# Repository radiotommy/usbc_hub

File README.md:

# usbc_hub
A 3-port usb hub.

It's part of my machenical keyboard with integrated hub project. This board stack at the back of my keyboard pcb with a 4 pin header as a usb port connect 
to my keyboard controller.

It's functional except USB3 only works in one orientation on the TypeC connector.

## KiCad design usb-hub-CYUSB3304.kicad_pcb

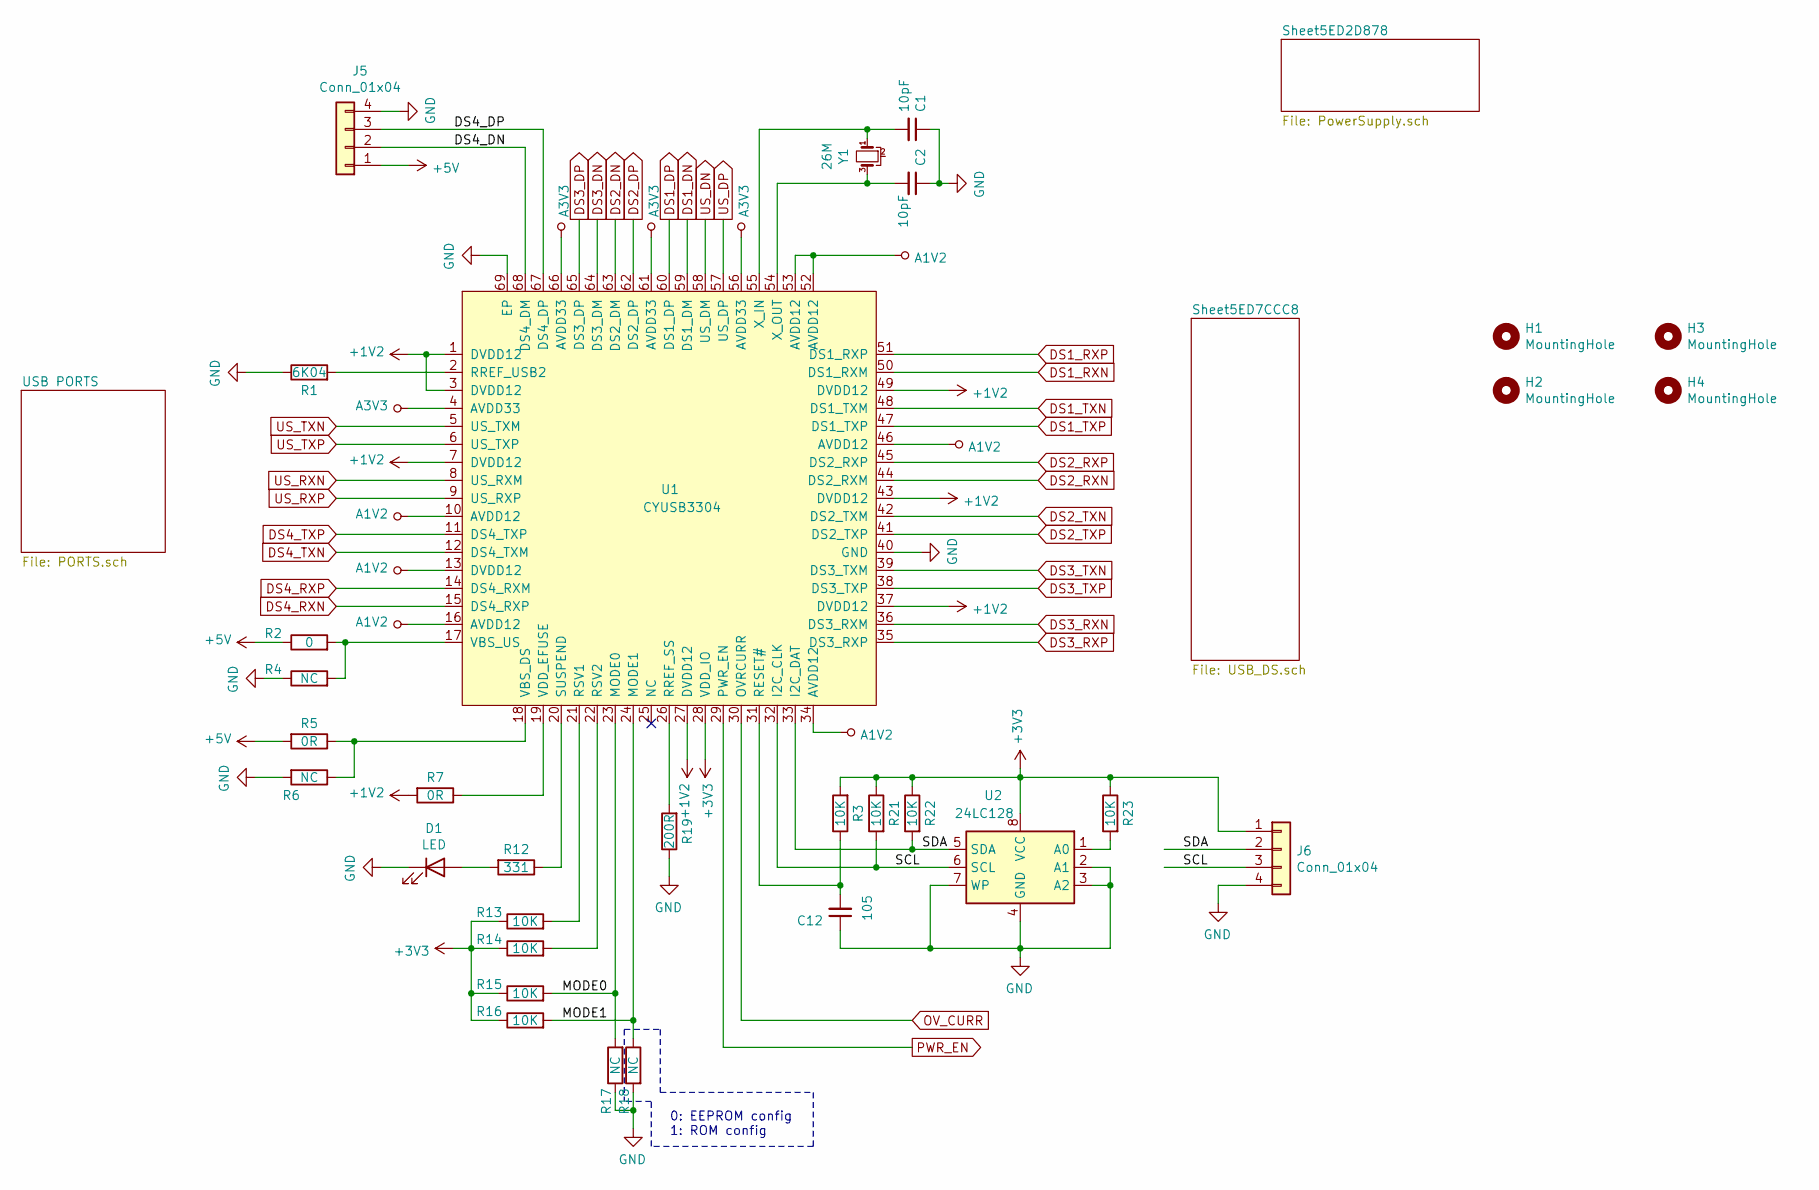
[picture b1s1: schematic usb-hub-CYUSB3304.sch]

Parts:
C1, C2: 10pF; C_0402_1005Metric
C12: 105; C_0402_1005Metric
D1: LED; LED_0805_2012Metric
H1, H2, H3, H4: MountingHole; MountingHole_2.5mm
J5, J6: Conn_01x04; PinHeader_1x04_P2.54mm_Vertical
R1: 6K04; R_0402_1005Metric
R2: 0; R_0402_1005Metric
R3, R13, R14, R15, R16, R21, R22, R23: 10K; R_0402_1005Metric
R4, R6, R17, R18: NC; R_0402_1005Metric
R5, R7: 0R; R_0402_1005Metric
R12: 331; R_0402_1005Metric
R19: 200R; R_0402_1005Metric
U1: CYUSB3304; QFN-68-1EP_8x8mm_P0.4mm_EP5.2x5.2mm_ThermalVias
U2: 24LC128; SO-8_3.9x4.9mm_P1.27mm
Y1: 26M; Crystal_SMD_2520-4Pin_2.5x2.0mm; PartNo ECS-260-10-36B-CKY-TR

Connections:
+1V2: R7.2, U1.1 (DVDD12), U1.3 (DVDD12), U1.7 (DVDD12), U1.27 (DVDD12), U1.37 (DVDD12), U1.43 (DVDD12), U1.49 (DVDD12); also elsewhere on the board
+3V3: J6.1, R3.2, R13.1, R14.1, R15.1, R16.1, R21.1, R22.1, R23.1, U1.28 (VDD_IO), U2.8 (VCC); also elsewhere on the board
+5V: J5.1, R2.1, R5.2; also elsewhere on the board
/DS4_DN: J5.2, U1.68 (DS4_DM)
/DS4_DP: J5.3, U1.67 (DS4_DP)
/MODE0: R15.2, R17.2, U1.23 (MODE0)
/MODE1: R16.2, R18.1, U1.24 (MODE1)
/SCL: J6.3, R21.2, U1.32 (I2C_CLK), U2.6 (SCL)
/SDA: J6.2, R22.2, U1.33 (I2C_DAT), U2.5 (SDA)
A1V2: U1.10 (AVDD12), U1.13 (DVDD12), U1.16 (AVDD12), U1.34 (AVDD12), U1.46 (AVDD12), U1.52 (AVDD12), U1.53 (AVDD12); also elsewhere on the board
A3V3: U1.4 (AVDD33), U1.56 (AVDD33), U1.61 (AVDD33), U1.66 (AVDD33); also elsewhere on the board
DS1_DN: U1.59 (DS1_DM); also elsewhere on the board
DS1_DP: U1.60 (DS1_DP); also elsewhere on the board
DS1_RXN: U1.50 (DS1_RXM); also elsewhere on the board
DS1_RXP: U1.51 (DS1_RXP); also elsewhere on the board
DS1_TXN: U1.48 (DS1_TXM); also elsewhere on the board
DS1_TXP: U1.47 (DS1_TXP); also elsewhere on the board
DS2_DN: U1.63 (DS2_DM); also elsewhere on the board
DS2_DP: U1.62 (DS2_DP); also elsewhere on the board
DS2_RXN: U1.44 (DS2_RXM); also elsewhere on the board
DS2_RXP: U1.45 (DS2_RXP); also elsewhere on the board
DS2_TXN: U1.42 (DS2_TXM); also elsewhere on the board
DS2_TXP: U1.41 (DS2_TXP); also elsewhere on the board
DS3_DN: U1.64 (DS3_DM); also elsewhere on the board
DS3_DP: U1.65 (DS3_DP); also elsewhere on the board
DS3_RXN: U1.36 (DS3_RXM); also elsewhere on the board
DS3_RXP: U1.35 (DS3_RXP); also elsewhere on the board
DS3_TXN: U1.39 (DS3_TXM); also elsewhere on the board
DS3_TXP: U1.38 (DS3_TXP); also elsewhere on the board
GND: C1.1, C2.1, C12.1, D1.1 (K), J5.4, J6.4, R1.1, R4.1, R6.2, R17.1, R18.2, R19.1, U1.40 (GND), U1.69 (EP), U2.2 (A1), U2.3 (A2), U2.4 (GND), U2.7 (WP); also elsewhere on the board
unnamed: C1.2, U1.55 (X_IN), Y1.1
unnamed: C2.2, U1.54 (X_OUT), Y1.3
unnamed: C12.2, R3.1, U1.31 (RESET#)
unnamed: D1.2 (A), R12.2
unnamed: R1.2, U1.2 (RREF_USB2)
unnamed: R2.2, R4.2, U1.17 (VBS_US)
unnamed: R5.1, R6.1, U1.18 (VBS_DS)
unnamed: R7.1, U1.19 (VDD_EFUSE)
unnamed: R12.1, U1.20 (SUSPEND)
unnamed: R13.2, U1.21 (RSV1)
unnamed: R14.2, U1.22 (RSV2)
unnamed: R19.2, U1.26 (RREF_SS)
unnamed: R23.2, U2.1 (A0)
OV_CURR: U1.30 (OVRCURR); also elsewhere on the board
PWR_EN: U1.29 (PWR_EN); also elsewhere on the board
US_DN: U1.58 (US_DM); also elsewhere on the board
US_DP: U1.57 (US_DP); also elsewhere on the board
US_RXN: U1.8 (US_RXM); also elsewhere on the board
US_RXP: U1.9 (US_RXP); also elsewhere on the board
US_TXN: U1.5 (US_TXM); also elsewhere on the board
US_TXP: U1.6 (US_TXP); also elsewhere on the board

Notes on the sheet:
0: EEPROM config 1: ROM config

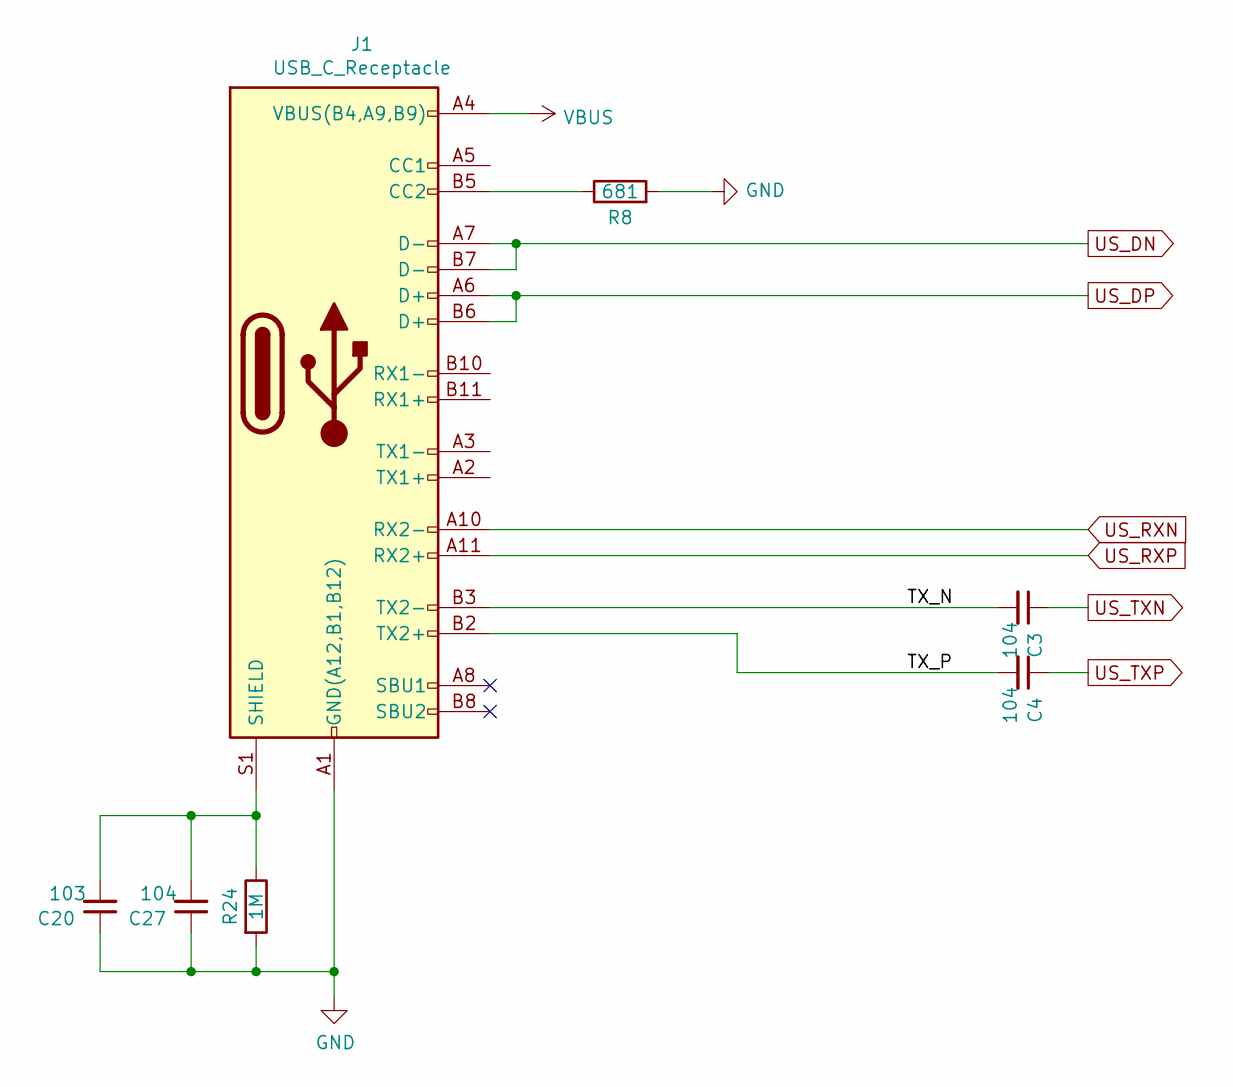
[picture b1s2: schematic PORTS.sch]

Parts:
C3, C4: 104; C_0402_1005Metric
C20: 103; C_0805_2012Metric
C27: 104; C_0805_2012Metric
J1: USB_C_Receptacle; USB_C_Receptacle_XKB_U262-241N-4BV60
R8: 681; R_0402_1005Metric
R24: 1M; R_0805_2012Metric

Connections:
/USB PORTS/TX_N: C3.2, J1.B3 (TX2-)
/USB PORTS/TX_P: C4.2, J1.B2 (TX2+)
GND: C20.1, C27.1, J1.A1 (GND(A12,B1,B12)), J1.A12 (GND), J1.B1 (GND), J1.B12 (GND), R8.2, R24.2; also elsewhere on the board
unnamed: C20.2, C27.2, J1.S1 (SHIELD), R24.1
unnamed: J1.B5 (CC2), R8.1
US_DN: J1.A7 (D-), J1.B7 (D-); also elsewhere on the board
US_DP: J1.A6 (D+), J1.B6 (D+); also elsewhere on the board
US_RXN: J1.A10 (RX2-); also elsewhere on the board
US_RXP: J1.A11 (RX2+); also elsewhere on the board
US_TXN: C3.1; also elsewhere on the board
US_TXP: C4.1; also elsewhere on the board
VBUS: J1.A4 (VBUS(B4,A9,B9)), J1.A9 (VBUS), J1.B4 (VBUS), J1.B9 (VBUS); also elsewhere on the board

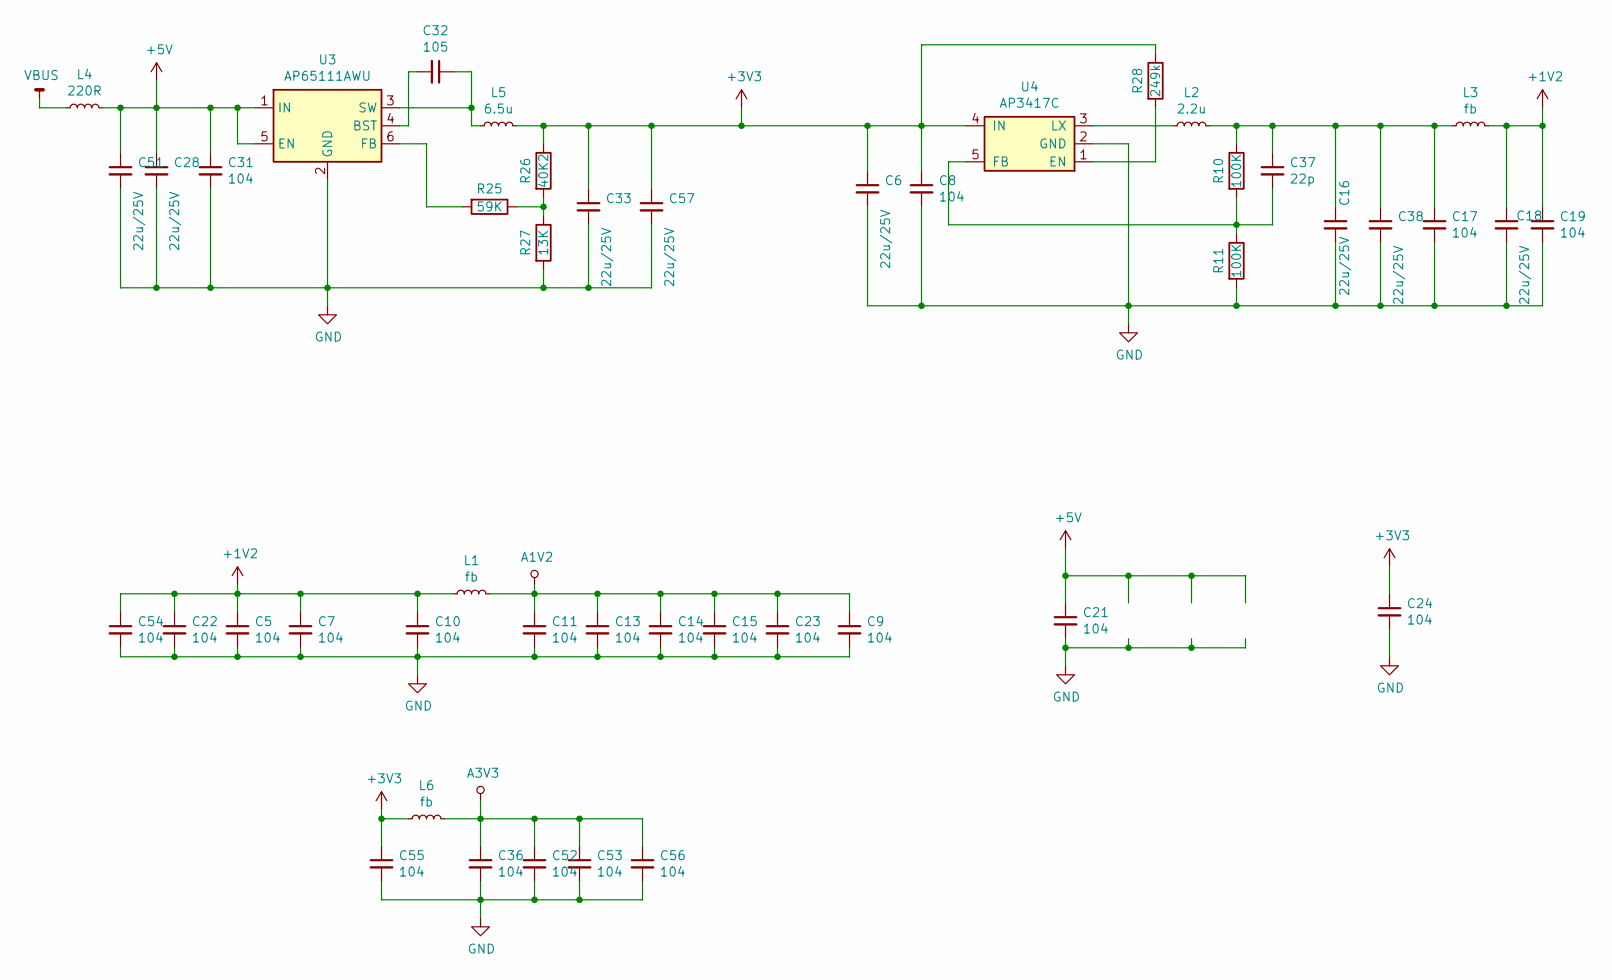
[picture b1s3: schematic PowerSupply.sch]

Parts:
C5, C7, C9, C10, C11, C13, C14, C15, C17, C19, C21, C22, C23, C24, C31, C36, C52, C53, C54, C55, C56: 104; C_0402_1005Metric
C6, C16, C18, C28, C33, C38, C51, C57: 22u/25V; C_1206_3216Metric
C8: 104; C_0603_1608Metric
C32: 105; C_0402_1005Metric
C37: 22p; C_0402_1005Metric
L1, L3, L6: fb; L_0805_2012Metric
L2: 2.2u; L_Bourns-SRN4018
L4: 220R; L_0805_2012Metric
L5: 6.5u; L_Bourns-SRN4018
R10, R11: 100K; R_0402_1005Metric
R25: 59K; R_0402_1005Metric
R26: 40K2; R_0402_1005Metric
R27: 13K; R_0402_1005Metric
R28: 249k; R_0402_1005Metric
U3: AP65111AWU; TSOT-23-6
U4: AP3417C; SOT-23-5

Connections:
+1V2: C5.1, C7.1, C10.1, C18.1, C19.1, C22.1, C54.1, L1.1, L3.2; also elsewhere on the board
+3V3: C6.1, C8.1, C24.1, C33.1, C55.1, C57.1, L5.2, L6.1, R26.1, R28.1, U4.4 (IN); also elsewhere on the board
+5V: C21.1, C28.1, C31.1, C51.1, L4.2, U3.1 (IN), U3.5 (EN); also elsewhere on the board
A1V2: C9.1, C11.1, C13.1, C14.1, C15.1, C23.1, L1.2; also elsewhere on the board
A3V3: C36.1, C52.1, C53.1, C56.1, L6.2; also elsewhere on the board
GND: C5.2, C6.2, C7.2, C8.2, C9.2, C10.2, C11.2, C13.2, C14.2, C15.2, C16.2, C17.2, C18.2, C19.2, C21.2, C22.2, C23.2, C24.2, C28.2, C31.2, C33.2, C36.2, C38.2, C51.2, C52.2, C53.2, C54.2, C55.2, C56.2, C57.2, R11.2, R27.2, U3.2 (GND), U4.2 (GND); also elsewhere on the board
unnamed: C16.1, C17.1, C37.1, C38.1, L2.2, L3.1, R10.1
unnamed: C32.1, L5.1, U3.3 (SW)
unnamed: C32.2, U3.4 (BST)
unnamed: C37.2, R10.2, R11.1, U4.5 (FB)
unnamed: L2.1, U4.3 (LX)
unnamed: R25.1, R26.2, R27.1
unnamed: R25.2, U3.6 (FB)
unnamed: R28.2, U4.1 (EN)
VBUS: L4.1; also elsewhere on the board

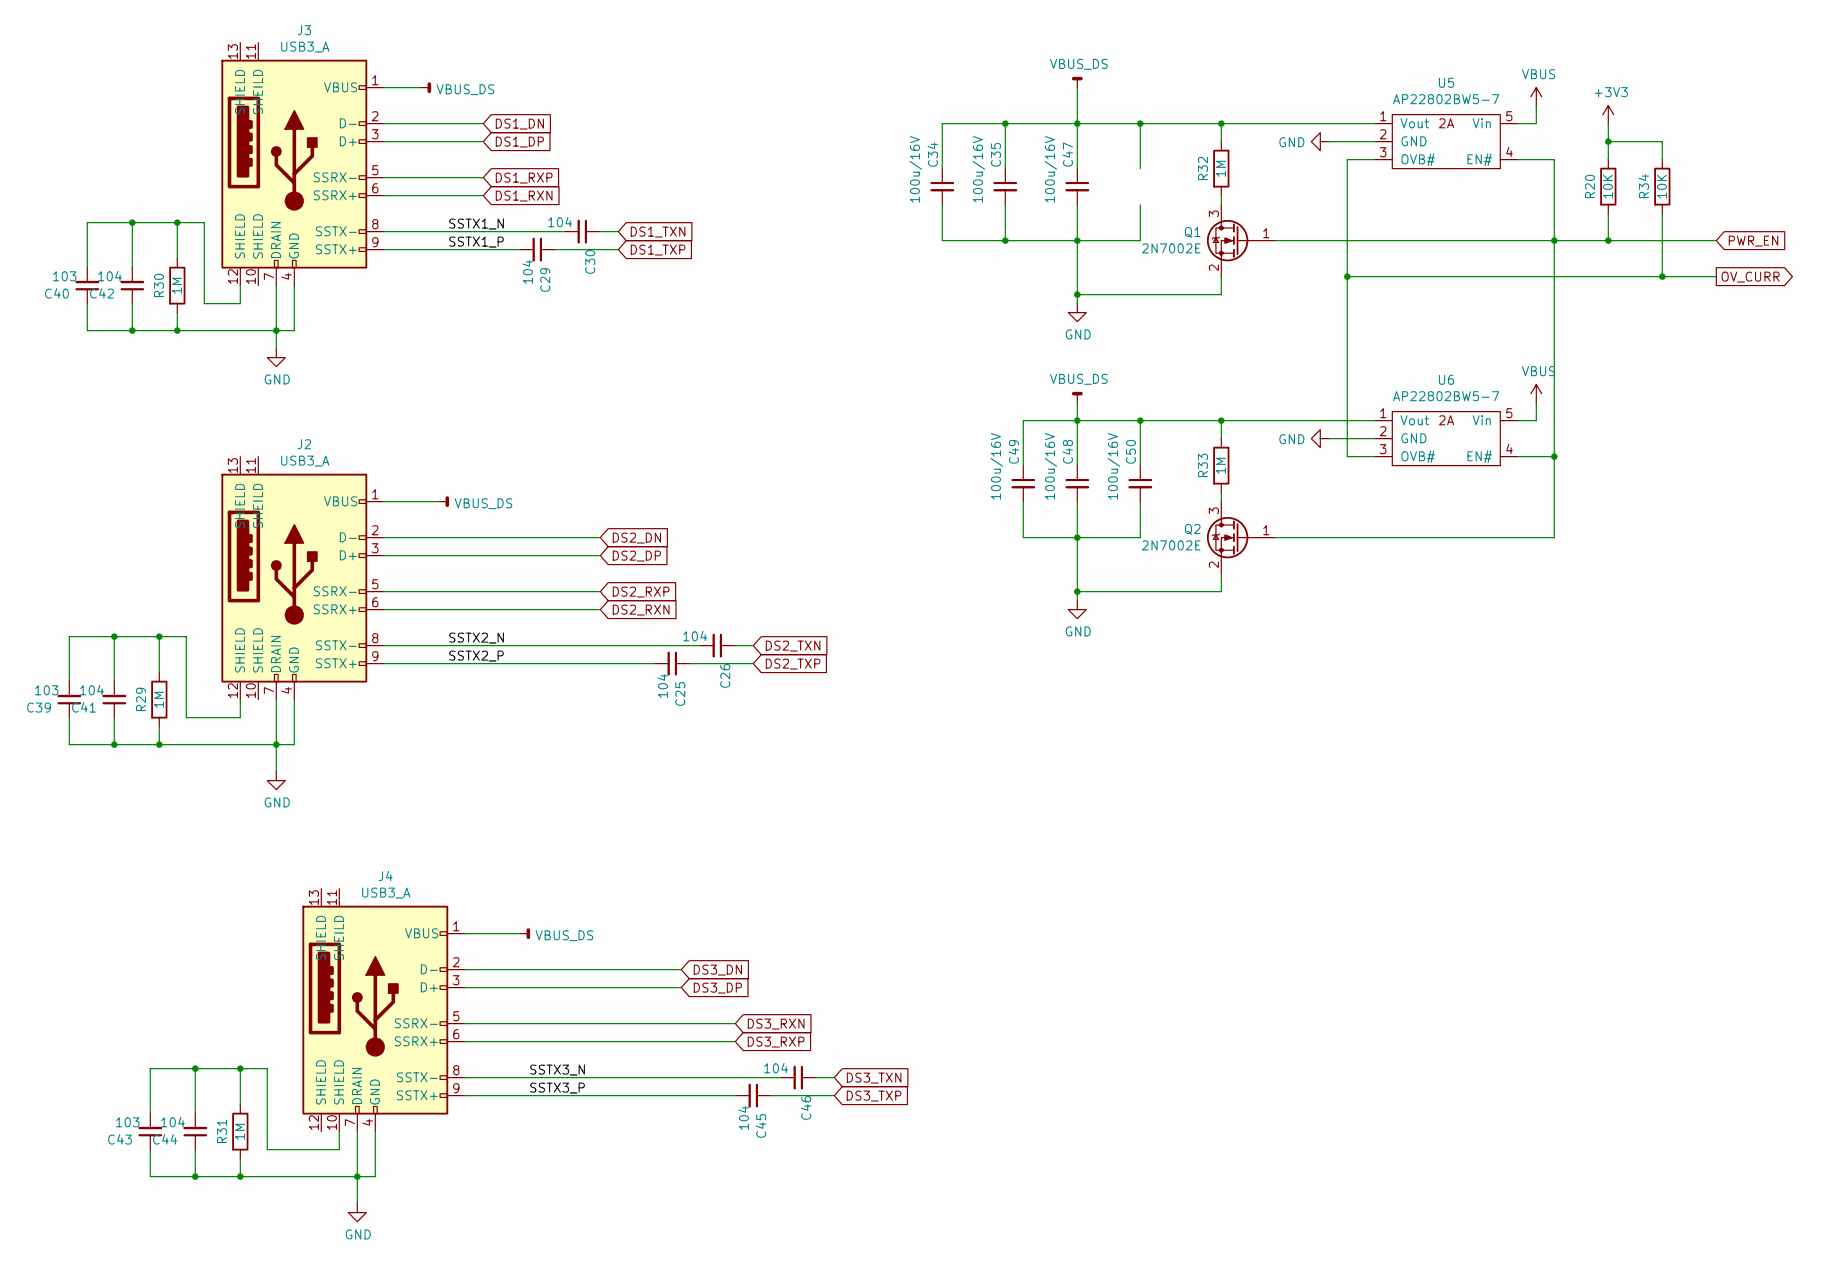
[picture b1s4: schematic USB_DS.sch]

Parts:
C25, C26, C29, C30, C45, C46: 104; C_0402_1005Metric
C34, C35, C47, C48, C49, C50: 100u/16V; C_1206_3216Metric
C39, C40, C43: 103; C_0805_2012Metric
C41, C42, C44: 104; C_0805_2012Metric
J2, J3, J4: USB3_A; USB3_A_XKB_U231-091N-3GRC10-5
Q1, Q2: 2N7002E; SOT-23
R20, R34: 10K; R_0402_1005Metric
R29, R30, R31, R32, R33: 1M; R_0805_2012Metric
U5, U6: AP22802BW5-7; SOT-23-5

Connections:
+3V3: R20.1, R34.1; also elsewhere on the board
/Sheet5ED7CCC8/SSTX1_N: C30.2, J3.8 (SSTX-)
/Sheet5ED7CCC8/SSTX1_P: C29.2, J3.9 (SSTX+)
/Sheet5ED7CCC8/SSTX2_N: C26.2, J2.8 (SSTX-)
/Sheet5ED7CCC8/SSTX2_P: C25.2, J2.9 (SSTX+)
/Sheet5ED7CCC8/SSTX3_N: C46.2, J4.8 (SSTX-)
/Sheet5ED7CCC8/SSTX3_P: C45.2, J4.9 (SSTX+)
DS1_DN: J3.2 (D-); also elsewhere on the board
DS1_DP: J3.3 (D+); also elsewhere on the board
DS1_RXN: J3.6 (SSRX+); also elsewhere on the board
DS1_RXP: J3.5 (SSRX-); also elsewhere on the board
DS1_TXN: C30.1; also elsewhere on the board
DS1_TXP: C29.1; also elsewhere on the board
DS2_DN: J2.2 (D-); also elsewhere on the board
DS2_DP: J2.3 (D+); also elsewhere on the board
DS2_RXN: J2.6 (SSRX+); also elsewhere on the board
DS2_RXP: J2.5 (SSRX-); also elsewhere on the board
DS2_TXN: C26.1; also elsewhere on the board
DS2_TXP: C25.1; also elsewhere on the board
DS3_DN: J4.2 (D-); also elsewhere on the board
DS3_DP: J4.3 (D+); also elsewhere on the board
DS3_RXN: J4.5 (SSRX-); also elsewhere on the board
DS3_RXP: J4.6 (SSRX+); also elsewhere on the board
DS3_TXN: C46.1; also elsewhere on the board
DS3_TXP: C45.1; also elsewhere on the board
GND: C34.2, C35.2, C39.1, C40.1, C41.1, C42.1, C43.1, C44.1, C47.2, C48.2, C49.2, C50.2, J2.4 (GND), J2.7 (DRAIN), J3.4 (GND), J3.7 (DRAIN), J4.4 (GND), J4.7 (DRAIN), Q1.2 (S), Q2.2 (S), R29.2, R30.2, R31.2, U5.2 (GND), U6.2 (GND); also elsewhere on the board
unnamed: C39.2, C41.2, J2.12 (SHIELD), R29.1
unnamed: C40.2, C42.2, J3.12 (SHIELD), R30.1
unnamed: C43.2, C44.2, J4.10 (SHIELD), R31.1
unnamed: Q1.3 (D), R32.2
unnamed: Q2.3 (D), R33.2
OV_CURR: R34.2, U5.3 (OVB#), U6.3 (OVB#); also elsewhere on the board
PWR_EN: Q1.1 (G), Q2.1 (G), R20.2, U5.4 (EN#), U6.4 (EN#); also elsewhere on the board
VBUS: U5.5 (Vin), U6.5 (Vin); also elsewhere on the board
VBUS_DS: C34.1, C35.1, C47.1, C48.1, C49.1, C50.1, J2.1 (VBUS), J3.1 (VBUS), J4.1 (VBUS), R32.1, R33.1, U5.1 (Vout), U6.1 (Vout)

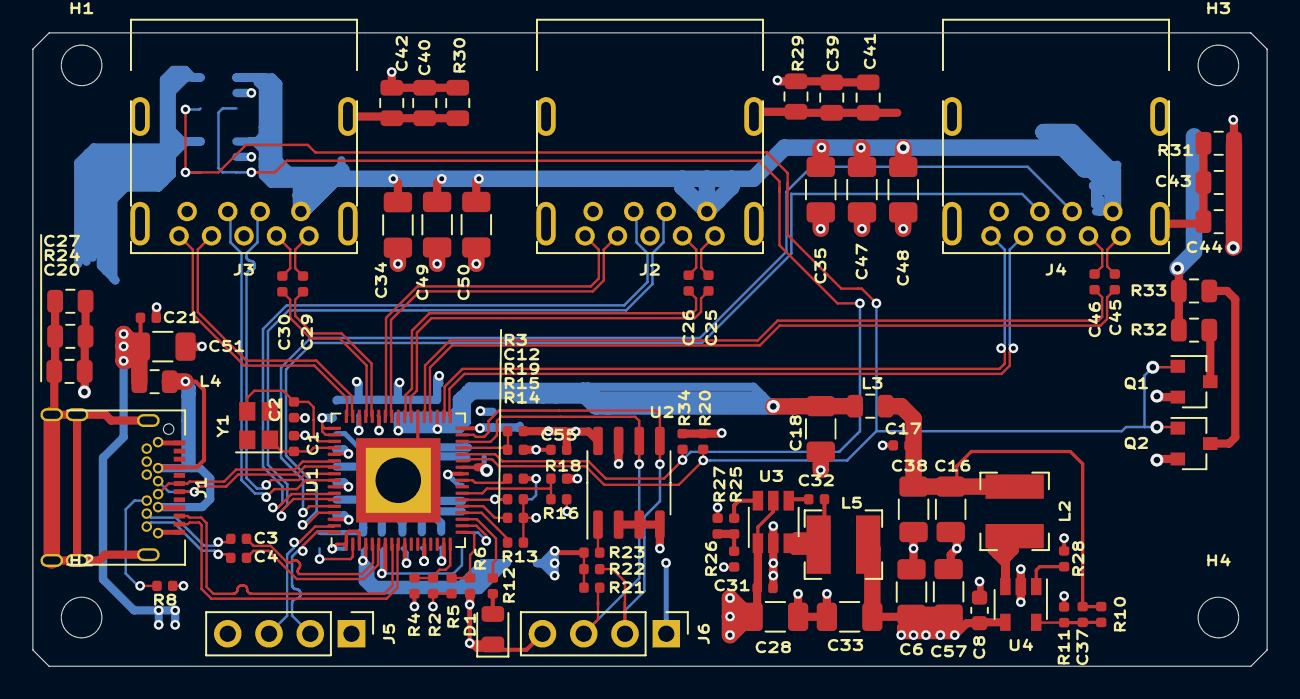
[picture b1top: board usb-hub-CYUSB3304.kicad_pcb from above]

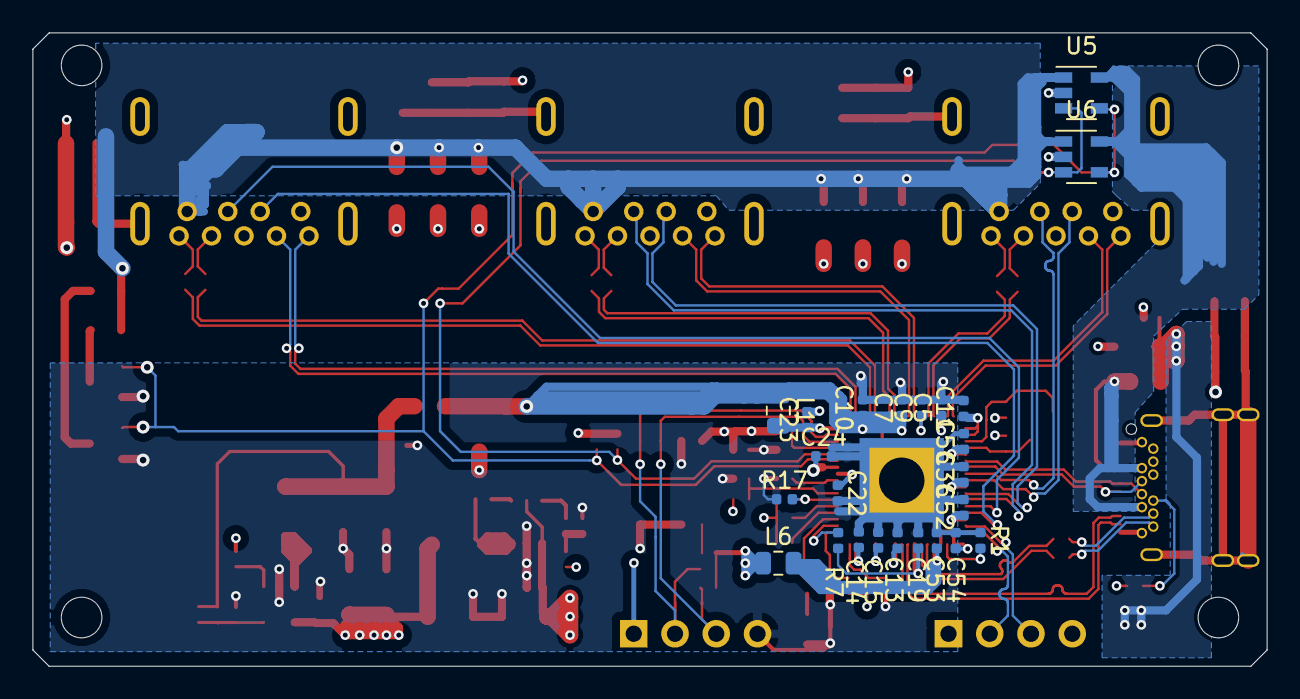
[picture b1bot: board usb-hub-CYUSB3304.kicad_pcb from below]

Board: 4 copper layers, 76.0 x 39.0 mm, 116 parts (24 on the bottom side), 76 nets.

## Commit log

2022-06-23 add lib cache
